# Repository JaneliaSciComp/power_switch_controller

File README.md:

# power_switch_controller

Authors:

    Peter Polidoro <polidorop@janelia.hhmi.org>

License:

    BSD

## More Detailed Help on Installation and Usage

[modular-devices](https://github.com/janelia-modular-devices/modular-devices)

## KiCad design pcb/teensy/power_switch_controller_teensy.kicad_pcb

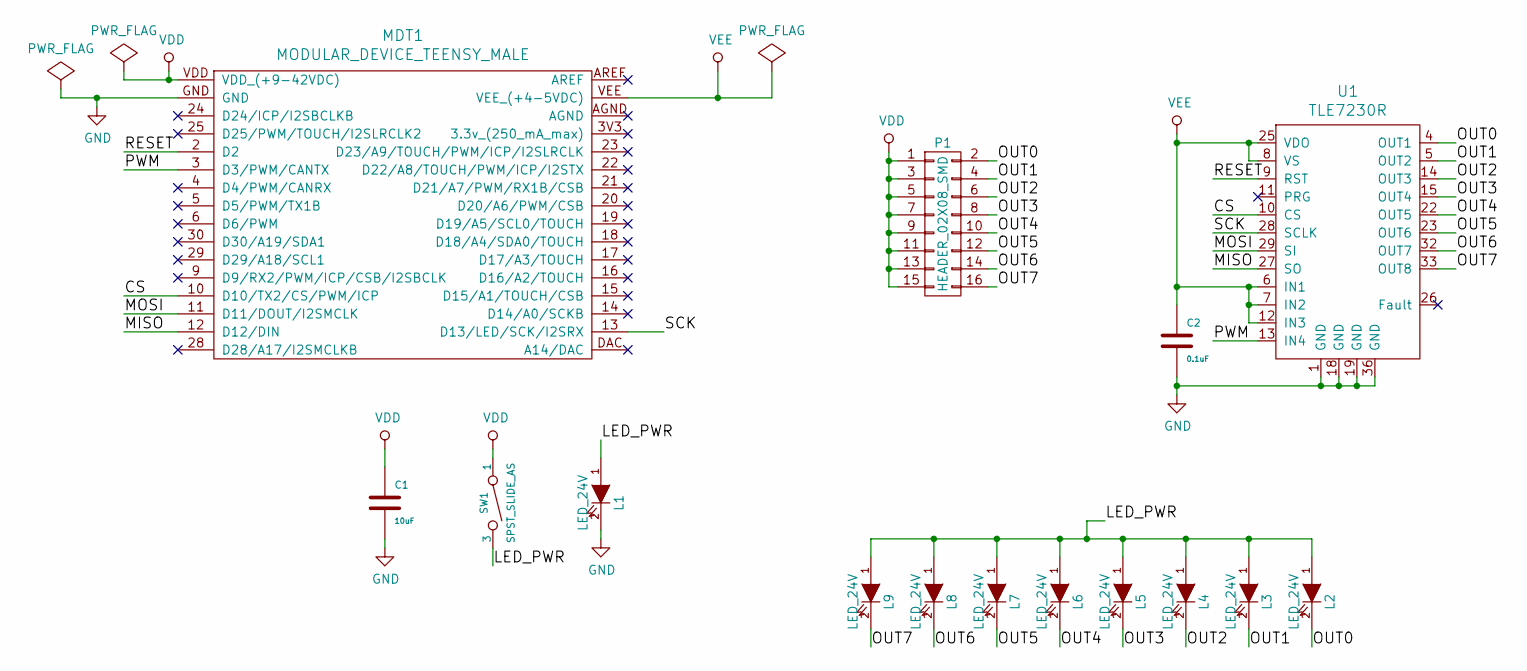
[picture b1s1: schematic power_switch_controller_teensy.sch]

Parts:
C1: 10uF; SM1210; PartNumber 445-4536-1-ND
C2: 0.1uF; SM1210; PartNumber 478-3586-1-ND
L1, L2, L3, L4, L5, L6, L7, L8, L9: LED_24V; LED_555-3XXX; PartNumber 350-1723-ND
MDT1: MODULAR_DEVICE_TEENSY_MALE; MODULAR_DEVICE_TEENSY; PartNumber S1011E-16-ND
P1: HEADER_02X08_SMD; HEADER_02x08_SMD; PartNumber S9187-ND
SW1: SPST_SLIDE_AS; PartNumber 360-2610-ND
U1: TLE7230R; PG-DSO-36; PartNumber TLE7230RCT-ND

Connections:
/CS: MDT1.10 (D10/TX2/CS/PWM/ICP), U1.10 (CS)
/LED_PWR: L1.1 (A), L2.1 (A), L3.1 (A), L4.1 (A), L5.1 (A), L6.1 (A), L7.1 (A), L8.1 (A), L9.1 (A), SW1.3
/MISO: MDT1.12 (D12/DIN), U1.27 (SO)
/MOSI: MDT1.11 (D11/DOUT/I2SMCLK), U1.29 (SI)
/OUT0: L2.2 (K), P1.2, U1.4 (OUT1)
/OUT1: L3.2 (K), P1.4, U1.5 (OUT2)
/OUT2: L4.2 (K), P1.6, U1.14 (OUT3)
/OUT3: L5.2 (K), P1.8, U1.15 (OUT4)
/OUT4: L6.2 (K), P1.10, U1.22 (OUT5)
/OUT5: L7.2 (K), P1.12, U1.23 (OUT6)
/OUT6: L8.2 (K), P1.14, U1.32 (OUT7)
/OUT7: L9.2 (K), P1.16, U1.33 (OUT8)
/PWM: MDT1.3 (D3/PWM/CANTX), U1.13 (IN4)
/RESET: MDT1.2 (D2), U1.9 (RST)
/SCK: MDT1.13 (D13/LED/SCK/I2SRX), U1.28 (SCLK)
GND: C1.2, C2.2, L1.2 (K), MDT1.GND, U1.1 (GND), U1.18 (GND), U1.19 (GND), U1.36 (GND)
VDD: C1.1, MDT1.VDD (VDD_(+9-42VDC)), P1.1, P1.3, P1.5, P1.7, P1.9, P1.11, P1.13, P1.15, SW1.1
VEE: C2.1, MDT1.VEE (VEE_(+4-5VDC)), U1.6 (IN1), U1.7 (IN2), U1.8 (VS), U1.12 (IN3), U1.25 (VDO)

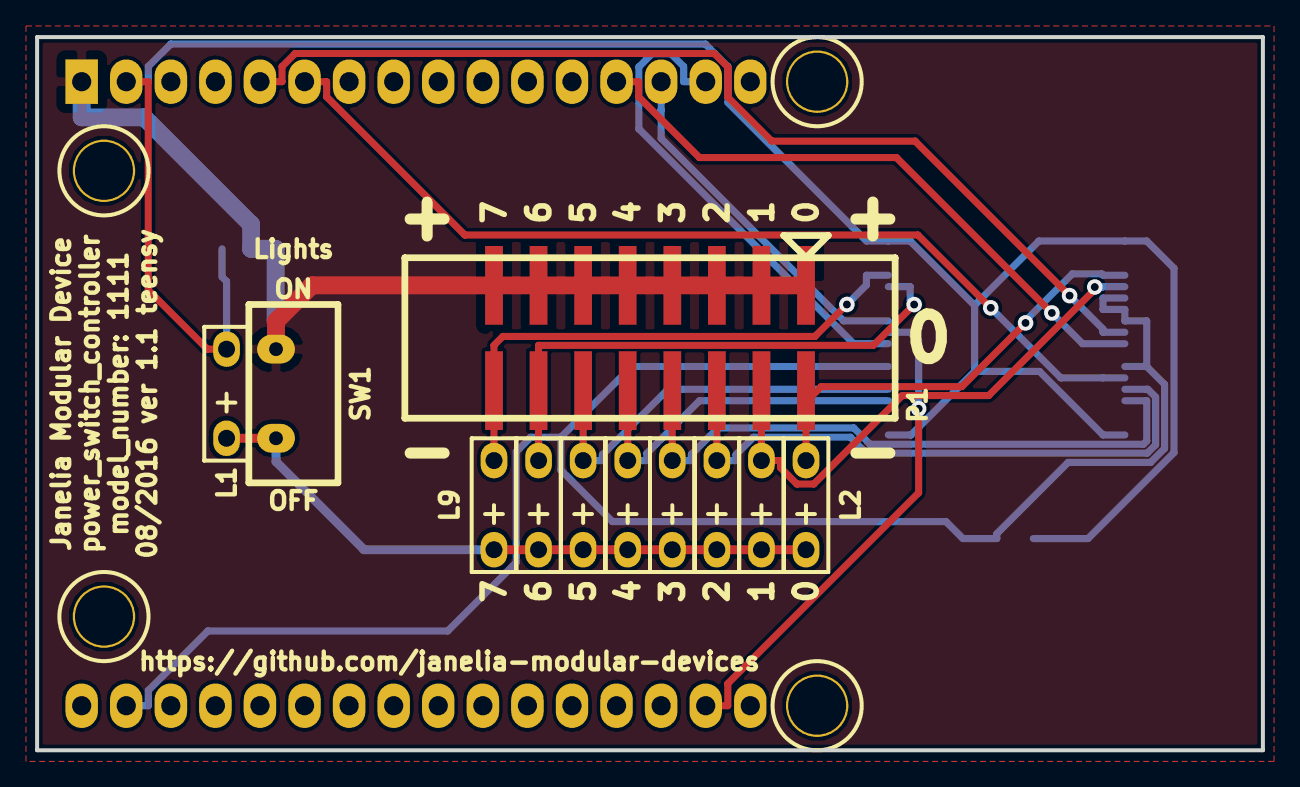
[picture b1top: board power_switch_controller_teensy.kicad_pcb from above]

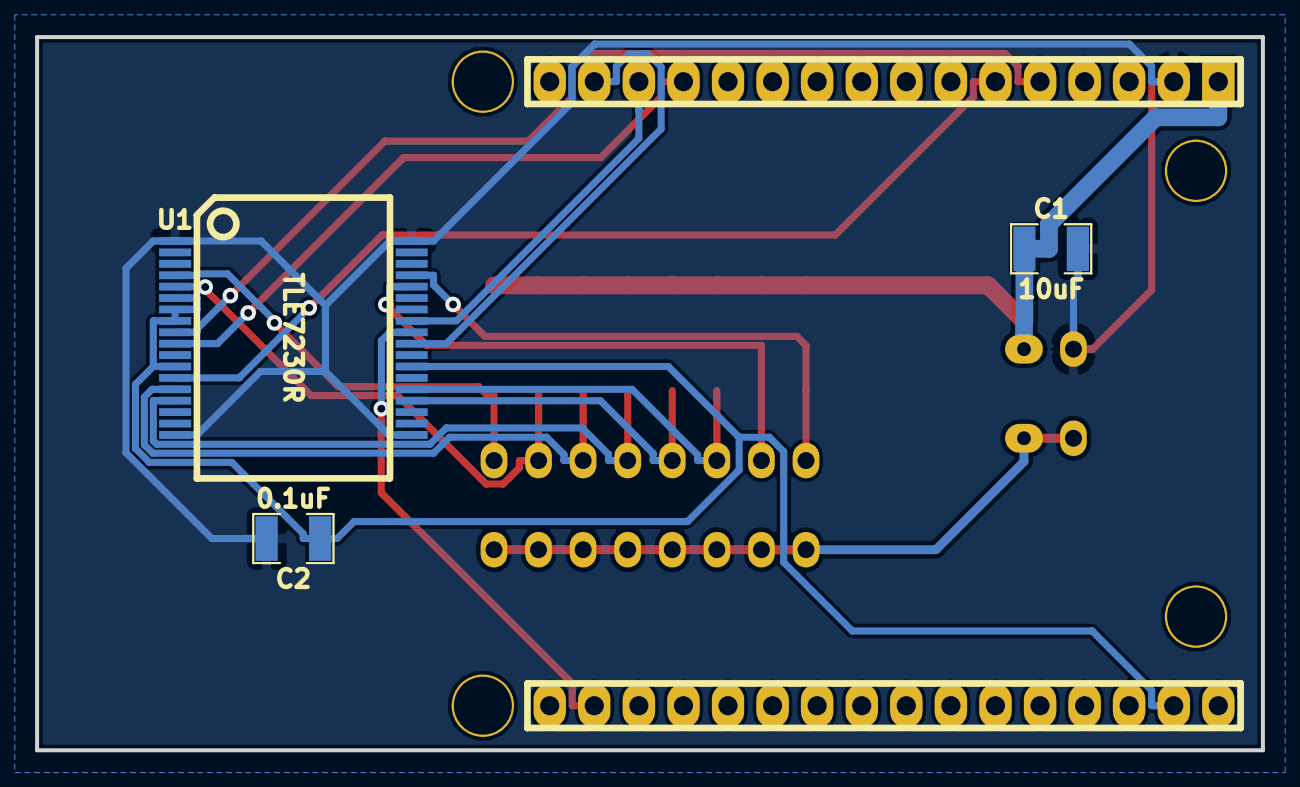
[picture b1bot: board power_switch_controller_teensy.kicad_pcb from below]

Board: 2 copper layers, 69.8 x 40.6 mm, 15 parts (3 on the bottom side), 18 nets.

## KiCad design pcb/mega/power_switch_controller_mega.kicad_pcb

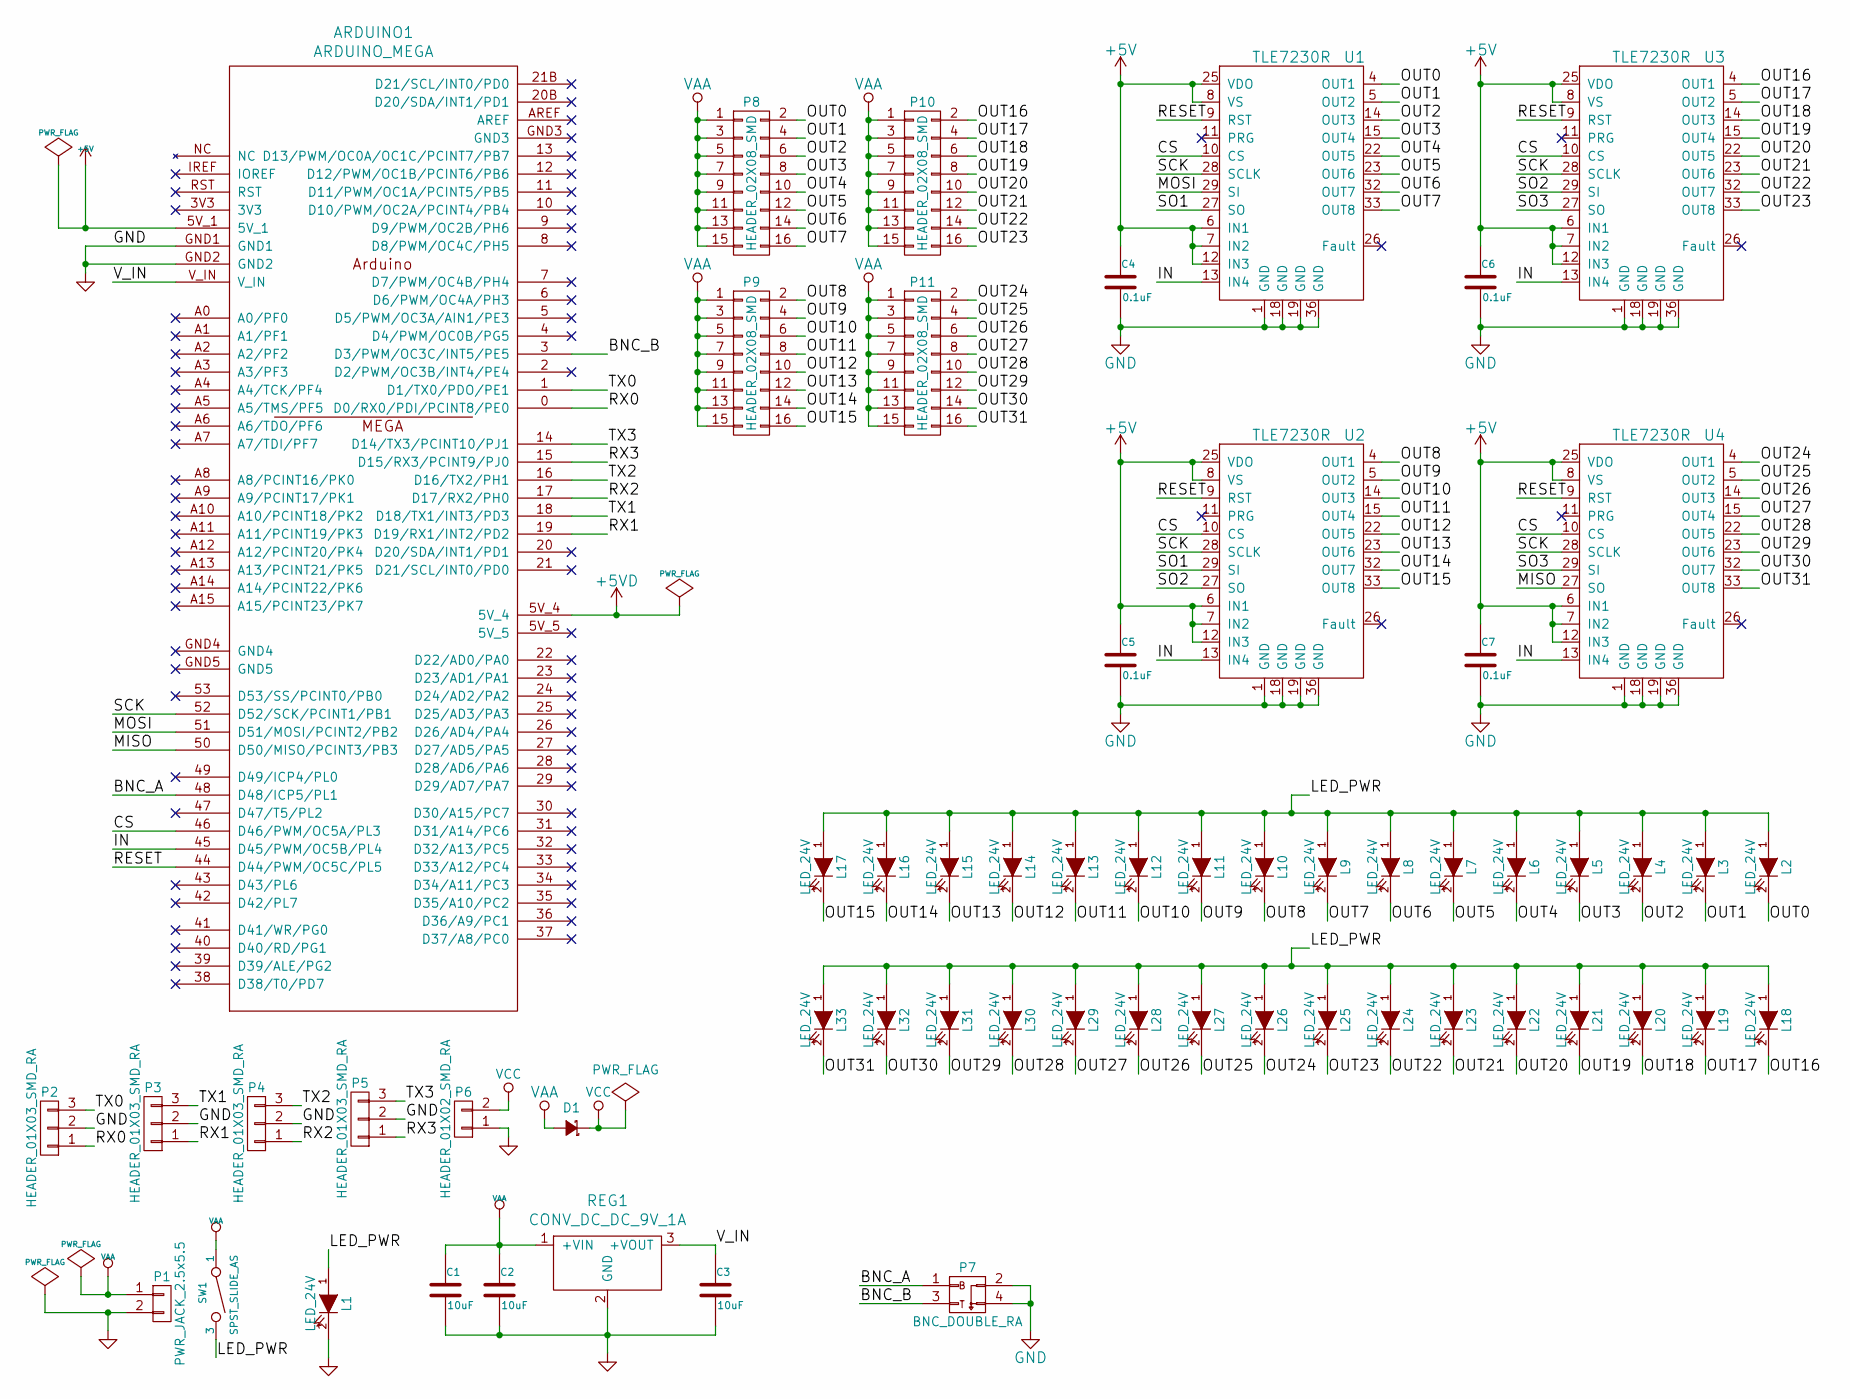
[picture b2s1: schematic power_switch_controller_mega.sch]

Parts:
ARDUINO1: ARDUINO_MEGA; ARDUINO_MEGA_SHIELD; PartNumber 1659-1001-ND
C1, C2, C3: 10uF; SM1210; PartNumber 445-4536-1-ND
C4, C5, C6, C7: 0.1uF; SM1210; PartNumber 478-3586-1-ND
D1: diode_schottky_45V_10A; CFP15; PartNumber 568-11697-1-ND
L1, L2, L3, L4, L5, L6, L7, L8, L9, L10, L11, L12, L13, L14, L15, L16, L17, L18, L19, L20, L21, L22, L23, L24, L25, L26, L27, L28, L29, L30, L31, L32, L33: LED_24V; LED_555-3XXX; PartNumber 350-1723-ND
P1: PWR_JACK_2.5x5.5; DCJACK_2PIN_HIGHCURRENT; PartNumber CP-063BH-ND
P2, P3, P4, P5: HEADER_01X03_SMD_RA; Header_3_Pin_SMD_RA; PartNumber A100890CT-ND
P6: HEADER_01X02_SMD_RA; Header_2_Pin_SMD_RA; PartNumber A100903CT-ND
P7: BNC_DOUBLE_RA; BNC_DOUBLE; PartNumber ACX1655-ND
P8, P9, P10, P11: HEADER_02X08_SMD; HEADER_02x08_SMD; PartNumber S9187-ND
REG1: CONV_DC_DC_9V_1A; DC_DC_CONV_R78C; PartNumber 945-1396-5-ND
SW1: SPST_SLIDE_AS; PartNumber 360-2610-ND
U1, U2, U3, U4: TLE7230R; PG-DSO-36; PartNumber TLE7230RCT-ND

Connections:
+5V: ARDUINO1.5V_1, C4.1, C5.1, C6.1, C7.1, U1.6 (IN1), U1.7 (IN2), U1.8 (VS), U1.12 (IN3), U1.25 (VDO), U2.6 (IN1), U2.7 (IN2), U2.8 (VS), U2.12 (IN3), U2.25 (VDO), U3.6 (IN1), U3.7 (IN2), U3.8 (VS), U3.12 (IN3), U3.25 (VDO), U4.6 (IN1), U4.7 (IN2), U4.8 (VS), U4.12 (IN3), U4.25 (VDO)
/BNC_A: ARDUINO1.48 (D48/ICP5/PL1), P7.1
/BNC_B: ARDUINO1.3 (D3/PWM/OC3C/INT5/PE5), P7.3
/CS: ARDUINO1.46 (D46/PWM/OC5A/PL3), U1.10 (CS), U2.10 (CS), U3.10 (CS), U4.10 (CS)
/IN: ARDUINO1.45 (D45/PWM/OC5B/PL4), U1.13 (IN4), U2.13 (IN4), U3.13 (IN4), U4.13 (IN4)
/LED_PWR: L1.1 (A), L2.1 (A), L3.1 (A), L4.1 (A), L5.1 (A), L6.1 (A), L7.1 (A), L8.1 (A), L9.1 (A), L10.1 (A), L11.1 (A), L12.1 (A), L13.1 (A), L14.1 (A), L15.1 (A), L16.1 (A), L17.1 (A), L18.1 (A), L19.1 (A), L20.1 (A), L21.1 (A), L22.1 (A), L23.1 (A), L24.1 (A), L25.1 (A), L26.1 (A), L27.1 (A), L28.1 (A), L29.1 (A), L30.1 (A), L31.1 (A), L32.1 (A), L33.1 (A), SW1.3
/MISO: ARDUINO1.50 (D50/MISO/PCINT3/PB3), U4.27 (SO)
/MOSI: ARDUINO1.51 (D51/MOSI/PCINT2/PB2), U1.29 (SI)
/OUT0: L2.2 (K), P8.2, U1.4 (OUT1)
/OUT1: L3.2 (K), P8.4, U1.5 (OUT2)
/OUT2: L4.2 (K), P8.6, U1.14 (OUT3)
/OUT3: L5.2 (K), P8.8, U1.15 (OUT4)
/OUT4: L6.2 (K), P8.10, U1.22 (OUT5)
/OUT5: L7.2 (K), P8.12, U1.23 (OUT6)
/OUT6: L8.2 (K), P8.14, U1.32 (OUT7)
/OUT7: L9.2 (K), P8.16, U1.33 (OUT8)
/OUT8: L10.2 (K), P9.2, U2.4 (OUT1)
/OUT9: L11.2 (K), P9.4, U2.5 (OUT2)
/OUT10: L12.2 (K), P9.6, U2.14 (OUT3)
/OUT11: L13.2 (K), P9.8, U2.15 (OUT4)
/OUT12: L14.2 (K), P9.10, U2.22 (OUT5)
/OUT13: L15.2 (K), P9.12, U2.23 (OUT6)
/OUT14: L16.2 (K), P9.14, U2.32 (OUT7)
/OUT15: L17.2 (K), P9.16, U2.33 (OUT8)
/OUT16: L18.2 (K), P10.2, U3.4 (OUT1)
/OUT17: L19.2 (K), P10.4, U3.5 (OUT2)
/OUT18: L20.2 (K), P10.6, U3.14 (OUT3)
/OUT19: L21.2 (K), P10.8, U3.15 (OUT4)
/OUT20: L22.2 (K), P10.10, U3.22 (OUT5)
/OUT21: L23.2 (K), P10.12, U3.23 (OUT6)
/OUT22: L24.2 (K), P10.14, U3.32 (OUT7)
/OUT23: L25.2 (K), P10.16, U3.33 (OUT8)
/OUT24: L26.2 (K), P11.2, U4.4 (OUT1)
/OUT25: L27.2 (K), P11.4, U4.5 (OUT2)
/OUT26: L28.2 (K), P11.6, U4.14 (OUT3)
/OUT27: L29.2 (K), P11.8, U4.15 (OUT4)
/OUT28: L30.2 (K), P11.10, U4.22 (OUT5)
/OUT29: L31.2 (K), P11.12, U4.23 (OUT6)
/OUT30: L32.2 (K), P11.14, U4.32 (OUT7)
/OUT31: L33.2 (K), P11.16, U4.33 (OUT8)
/RESET: ARDUINO1.44 (D44/PWM/OC5C/PL5), U1.9 (RST), U2.9 (RST), U3.9 (RST), U4.9 (RST)
/RX0: ARDUINO1.0 (D0/RX0/PDI/PCINT8/PE0), P2.1
/RX1: ARDUINO1.19 (D19/RX1/INT2/PD2), P3.1
/RX2: ARDUINO1.17 (D17/RX2/PH0), P4.1
/RX3: ARDUINO1.15 (D15/RX3/PCINT9/PJ0), P5.1
/SCK: ARDUINO1.52 (D52/SCK/PCINT1/PB1), U1.28 (SCLK), U2.28 (SCLK), U3.28 (SCLK), U4.28 (SCLK)
/SO1: U1.27 (SO), U2.29 (SI)
/SO2: U2.27 (SO), U3.29 (SI)
/SO3: U3.27 (SO), U4.29 (SI)
/TX0: ARDUINO1.1 (D1/TX0/PDO/PE1), P2.3
/TX1: ARDUINO1.18 (D18/TX1/INT3/PD3), P3.3
/TX2: ARDUINO1.16 (D16/TX2/PH1), P4.3
/TX3: ARDUINO1.14 (D14/TX3/PCINT10/PJ1), P5.3
/V_IN: ARDUINO1.V_IN, C3.1, REG1.3 (+VOUT)
GND: ARDUINO1.GND1, ARDUINO1.GND2, C1.2, C2.2, C3.2, C4.2, C5.2, C6.2, C7.2, L1.2 (K), P1.2, P2.2, P3.2, P4.2, P5.2, P6.1, P7.2, P7.4, REG1.2 (GND), U1.1 (GND), U1.18 (GND), U1.19 (GND), U1.36 (GND), U2.1 (GND), U2.18 (GND), U2.19 (GND), U2.36 (GND), U3.1 (GND), U3.18 (GND), U3.19 (GND), U3.36 (GND), U4.1 (GND), U4.18 (GND), U4.19 (GND), U4.36 (GND)
VAA: C1.1, C2.1, D1.2 (A), P1.1, P8.1, P8.3, P8.5, P8.7, P8.9, P8.11, P8.13, P8.15, P9.1, P9.3, P9.5, P9.7, P9.9, P9.11, P9.13, P9.15, P10.1, P10.3, P10.5, P10.7, P10.9, P10.11, P10.13, P10.15, P11.1, P11.3, P11.5, P11.7, P11.9, P11.11, P11.13, P11.15, REG1.1 (+VIN), SW1.1
VCC: D1.1 (K), P6.2

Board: 2 copper layers, 59 parts (13 on the bottom side), 57 nets, no tracks yet.

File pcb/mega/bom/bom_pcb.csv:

Item,Reference(s),Value,Quantity,Description,PartNumber,Vendor
1,ARDUINO1,ARDUINO_MEGA,1,ARDUINO MEGA 2560,1659-1001-ND,digikey
2,C1 C2 C3,10uF,3,CAP CER 10UF 50V 10% X7S 1210,445-4536-1-ND,digikey
3,C4 C5 C6 C7 C8,0.1uF,5,CAP CER 0.1UF 50V 10% X7R 1210,478-3586-1-ND,digikey
4,D1,diode_schottky_45V_10A,1,DIODE SCHOTTKY 45V 10A CFP15,568-11697-1-ND,digikey
5,L1 L10 L11 L12 L13 L14 L15 L16 L17 L18 L19 L2 L20 L21 L22 L23 L24 L25 L26 L27 L28 L29 L3 L30 L31 L32 L33 L4 L5 L6 L7 L8 L9,LED_24V,33,LED 2MM 24V VERTICAL RED PC MNT,350-1723-ND,digikey
6,P1,PWR_JACK_2.5x5.5,1,CONN PWR JACK DC 2.5X5.5 8A T/H,CP-063BH-ND,digikey
7,P10 P11 P8 P9,HEADER_02X08_SMD,4,CONN HEADR 2.54MM 16POS GOLD SMD,S9187-ND,digikey
8,P2 P3 P4 P5,HEADER_01X03_SMD_RA,4,CONN HEADER 3POS R/A SMD GOLD,A100890CT-ND,digikey
9,P6,HEADER_01X02_SMD_RA,1,CONN HEADER 2POS R/A SMD GOLD,A100903CT-ND,digikey
10,P7,BNC_DOUBLE_RA,1,CONN BNC JACK R/A 75 OHM PCB,ACX1655-ND,digikey
11,R1 R2,10.0k,2,RES SMD 10.0K OHM 1% 1/2W 1210,P10.0KAACT-ND,digikey
12,REG1,CONV_DC_DC_9V_1A,1,CONV DC/DC 1A 9V OUT SIP VERT,945-1396-5-ND,digikey
13,SW1,SPST_SLIDE_AS,1,SWITCH SLIDE SPST 0.4VA 28V,360-2610-ND,digikey
14,U1 U2 U3 U4,TLE7230R,4,IC SW SMART OCTAL LOWSIDE PDSO36,TLE7230RCT-ND,digikey
15,U5,PCA9685,1,LED Driver IC 16 Output Linear PWM Dimming 25mA 28-TSSOP,568-5931-1-ND,digikey

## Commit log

2014-11-21 Initial commit.
2014-11-25 Pcb file setup.
2014-12-12 Initial design setup.
2015-01-05 Made design changes preparing for version 1.0.
2015-01-06 Changed connectors to 2x16 header.
2015-01-08 Moved components on pcb.
2015-01-08 Finished pcb version 1.0
2015-01-09 Added schematic pdf.
2015-01-09 Added schematic svg.
2015-01-14 Initial firmware commit.
2015-01-15 Some firmware methods implemented.
2015-01-16 Progress on firmware for pcb v1.0.
2015-01-20 Progress towards 32 power switches.
2015-01-21 Finished pcb v1.1.
2015-01-28 remote -> modular.
2015-01-28 Updated ic_count and channel_count.
2015-02-06 Moved modular_device setup into power_switch_controller.
2015-02-06 Reorganized and added Methods.
2015-02-07 Added four methods.
2015-02-09 Fixed typos and added toggleAllChannels method.
2015-02-10 Updated documentation.
2015-02-10 Added saveState, recallState, and getSavedStates.
2015-02-13 Added initial StandaloneInterface.
2015-02-13 Added more StandAlone frames.
2015-02-16 Modified to match new right justify behavior.
2015-02-18 pcb v1.2.
2015-02-20 Changed spacing.
2015-02-20 Added #include "BetterMap.h".
2015-02-23 Modified how states_array gets passed to method.
2015-02-23 Made dsp_vars local variables instead of class variable.s
2015-02-23 Modified spacing.
2015-02-23 Changed local pointers to local references.
2015-02-23 Slight reorganization.
2015-03-19 StandardCplusplus -> array. Updated pin constants.
2015-03-19 Made display_serial a reference.
2015-03-24 Use new libraries ConstantVariable and SavedVariable.
2015-03-27 Added images.
2015-04-15 Added addPulseCentered method.
2015-04-16 Testing.
2015-04-16 Added addPwmPeriodOnDuration method.
2015-04-16 In the middle of adding addPwmFrequencyDutyCycle method.
2015-04-17 Added addSpikeAndHold method.
2015-04-17 Added stopAllEvents method.
2015-04-17 Added start and stop event methods.
2015-04-18 stopAllEvents -> stopAllPulses. stopEvent -> stopPulseWave.
2015-04-18 Added new frames.
2015-04-18 spikeAndHold -> spikeHold
2015-04-19 pulse_index -> pulse_wave_index.
2015-04-21 setFlashString -> setConstantString.
2015-04-21 Updated README.
2015-04-22 Added spikeHold standalone frame.
2015-04-22 Partially updated pwm frame.
2015-04-22 Finished pwm standalone frame.
2015-04-24 Added LICENSE.
2015-05-08 Increased states from 10 to 16.
2015-07-13 JaneliaSciComp -> janelia-modular-devices.
2015-07-24 Updated author/license.
2015-07-24 Moved README info.
2015-07-28 boolean -> bool.
2015-08-10 SPST switch -> DPST switch.
2015-08-10 Updated digikey_order_add.
2015-09-09 led_pwr_pin -> lights_pin.
2015-09-09 Kicad update.
2015-10-02 New digikey order for multiple modular devices.
2015-10-16 Added GenericSerial.
2015-10-22 Updated to match changes in ModularDevice.
2015-12-11 ModularDevice -> ModularServer.
2015-12-11 ModularStandalone -> StandaloneInterface.
2016-01-08 Progress towards array -> vector.
2016-01-11 Made some changes, but not working at this commit.
2016-01-12 External vectors working.
2016-02-24 Progress towards pcb v1.4.
2016-02-26 Updated bom.
2016-02-29 Added TLE5X.
2016-03-03 Finished pcb v1.5.
2016-03-03 Updated discontinued part.
2016-03-09 Separated standalone firmware from device firmware.
2016-03-10 Updated images.
2016-06-21 Create mega pcb.
2016-06-21 Progress towards mega pcb 1.6.
2016-06-22 Finished pcb 1.6.
2016-06-23 Updated Arduino Mega digikey part number.
2016-07-01 Updated firmware to handle fields.
2016-07-13 Progess towards mega pcb1.7.
2016-07-15 Modified text size.
2016-07-18 Changed power supply.
2016-07-18 Initial add of pcb/teensy.
2016-07-18 Progress towards teensy v1.0.
2016-07-20 More progress towards v1.0.
2016-07-25 Finished teensy pcb v1.0.
2016-08-09 Removed obsolete footprint.
2016-08-17 Modified firmware to work with teensy hardware.
2016-09-19 Updated spaces around pointers and references.
2016-09-21 pcb -> hardware.
2016-12-05 Upgraded firmware from 1.0 to 2.0.
2016-12-14 Updated firmware/PowerSwitchController.
2017-08-08 Removed old hardware files.
2017-08-08 Added hardware submodules.
2017-08-24 Updated firmware.
2018-04-12 Updated submodules.
2018-04-12 *.md -> *.org.
2018-05-18 Submodule update.
2018-07-11 Added generate_modular_device_documentation submodule.
2018-07-11 Added project.org.
2018-08-12 polidorop@janelia.hhmi.org -> peterpolidoro@gmail.com
2018-08-27 Combined software and hardware licenses.
2021-09-17 Update email address
